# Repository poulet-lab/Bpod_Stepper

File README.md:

# Bpod Stepper Module

The *Bpod Stepper Module* enables virtually noiseless operation of a stepper motor by combining smooth acceleration profiles with a *SilentStepStick* driver. You can use it either as a module for *Bpod state machine r2* or as a stand-alone USB device.

## Wiki

Please refer to [**the wiki**](../../wiki) for documentation.

## Credits ##

* Concept & firmware by Florian Rau and Josh Sanders
* PCB layout by Christopher Schultz, Josh Sanders and Florian Rau
* PCB layout partially based on:
  * [Bpod Teensy Shield](https://github.com/sanworks/Bpod-CAD/tree/master/PCB/Modules/Gen2/Bpod%20Teensy%20Shield) by Sanworks ([GPL v3](https://www.gnu.org/licenses/gpl-3.0.en.html))
  * [SilentStepStick Protector](https://github.com/watterott/SilentStepStick) by Watterott ([CC BY-SA 4.0](https://creativecommons.org/licenses/by-sa/4.0/))
* Library dependencies:
  * [ArCOM](https://github.com/bimac/ArCOM) by Sanworks ([GPL v3](https://www.gnu.org/licenses/gpl-3.0.en.html))
  * [TeensyStep](https://github.com/luni64/TeensyStep) by luni64 ([MIT](https://opensource.org/licenses/MIT))
  * [TMCStepper](https://github.com/teemuatlut/TMCStepper) by teemuatlut ([MIT](https://opensource.org/licenses/MIT))
  * [Teensy3x_QuadDecode](https://github.com/bimac/Teensy3x_QuadDecode.git) by TLB ([MIT](https://opensource.org/licenses/MIT))

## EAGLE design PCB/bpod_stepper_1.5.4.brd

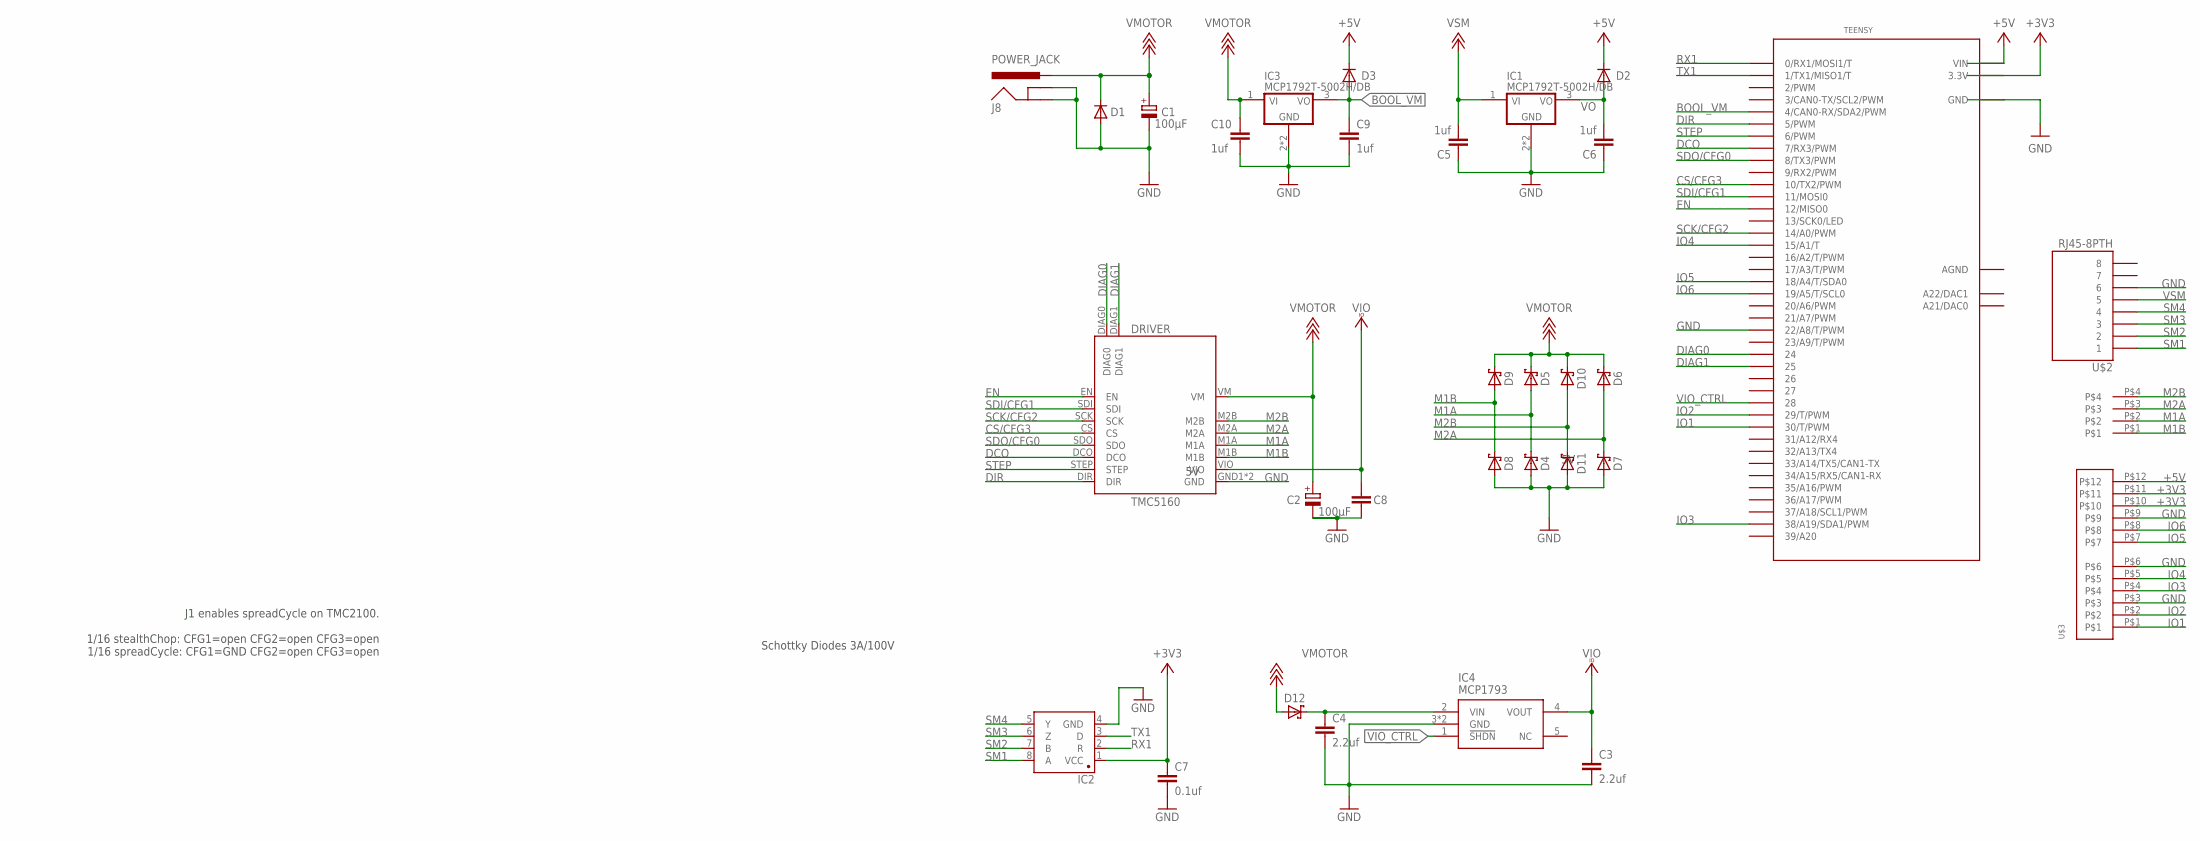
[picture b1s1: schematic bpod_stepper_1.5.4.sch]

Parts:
C1, C2: 100µF; PANASONIC_G
C3, C4: 2.2uf; 1206@1
C5, C6, C9, C10: 1uf; 1206@1
C7: 0.1uf; 1206@1
C8: 100nf; 1206@1
D1: DIODE-DO214AA; DO214AA
D2, D3: MBR0520LT; SOD123
D4, D5, D6, D7, D8, D9, D10, D11, D12: S310FA; SOD123
DRIVER: TMC5160
IC1, IC3: MCP1792T-5002H/DB; SOT223
IC2: SN65HVD31DR; SO08
IC4: MCP1793; SOT223-5
J8: POWER_JACK; POWER_JACK_PTH
TEENSY: TEENSY_3.6_DIL
U$2: RJ45-8PTH; RJ45-8
U$3: 12POS_MOLEX_SOCKET
U$4: MOLEX395221004

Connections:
+3V3: C7.1, IC2.1 (VCC), TEENSY.3.3V, TEENSY.3.3V3 (3.3V), U$3.P$10, U$3.P$11
+5V: D2.C, D3.C, TEENSY.VIN, U$3.P$12
AGND: TEENSY.AGND
BOOL_VM: C9.1, D3.A, IC3.3 (VO), TEENSY.4 (4/CAN0-RX/SDA2/PWM)
CS/CFG3: DRIVER.CS, TEENSY.10 (10/TX2/PWM)
DCO: DRIVER.DCO, TEENSY.7 (7/RX3/PWM)
DIAG0: DRIVER.DIAG0, TEENSY.24
DIAG1: DRIVER.DIAG1, TEENSY.25
DIR: DRIVER.DIR, TEENSY.5 (5/PWM)
EN: DRIVER.EN, TEENSY.12 (12/MISO0)
GND: C1.-, C2.-, C3.2, C4.2, C5.1, C6.1, C7.2, C8.2, C9.2, C10.2, D1.A, D4.A, D7.A, D8.A, D11.A, DRIVER.GND1 (GND), DRIVER.GND2 (GND), IC1.2 (GND), IC1.4 (GND), IC2.4 (GND), IC3.2 (GND), IC3.4 (GND), IC4.3 (GND), IC4.6 (GND), J8.GND, J8.GNDBREAK, TEENSY.22/A8 (22/A8/T/PWM), TEENSY.GND, TEENSY.GND1 (GND), U$2.6, U$3.P$3, U$3.P$6, U$3.P$9
IO1: TEENSY.30 (30/T/PWM), U$3.P$1
IO2: TEENSY.29 (29/T/PWM), U$3.P$2
IO3: TEENSY.38/A19 (38/A19/SDA1/PWM), U$3.P$4
IO4: TEENSY.15/A1 (15/A1/T), U$3.P$5
IO5: TEENSY.18/A4 (18/A4/T/SDA0), U$3.P$7
IO6: TEENSY.19/A5 (19/A5/T/SCL0), U$3.P$8
M1A: D4.C, D5.A, DRIVER.M1A, U$4.P$2
M1B: D8.C, D9.A, DRIVER.M1B, U$4.P$1
M2A: D6.A, D7.C, DRIVER.M2A, U$4.P$3
M2B: D10.A, D11.C, DRIVER.M2B, U$4.P$4
unnamed: C4.1, D12.C, IC4.2 (VIN)
RX1: IC2.2 (R), TEENSY.0 (0/RX1/MOSI1/T)
SCK/CFG2: DRIVER.SCK, TEENSY.14/A0 (14/A0/PWM)
SDI/CFG1: DRIVER.SDI, TEENSY.11 (11/MOSI0)
SDO/CFG0: DRIVER.SDO, TEENSY.8 (8/TX3/PWM)
SM1: IC2.8 (A), U$2.1
SM2: IC2.7 (B), U$2.2
SM3: IC2.6 (Z), U$2.3
SM4: IC2.5 (Y), U$2.4
STEP: DRIVER.STEP, TEENSY.6 (6/PWM)
TX1: IC2.3 (D), TEENSY.1 (1/TX1/MISO1/T)
VIO: C3.1, C8.1, DRIVER.VIO, IC4.4 (VOUT)
VIO_CTRL: IC4.1 (!SHDN), TEENSY.28
VMOTOR: C1.+, C2.+, C10.1, D1.C, D5.C, D6.C, D9.C, D10.C, D12.A, DRIVER.VM, IC3.1 (VI), J8.PWR
VO: C6.2, D2.A, IC1.3 (VO)
VSM: C5.2, IC1.1 (VI), U$2.5

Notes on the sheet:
Schottky Diodes 3A/100V
J1 enables spreadCycle on TMC2100. 1/16 stealthChop: CFG1=open CFG2=open CFG3=open 1/16 spreadCycle: CFG1=GND CFG2=open CFG3=open

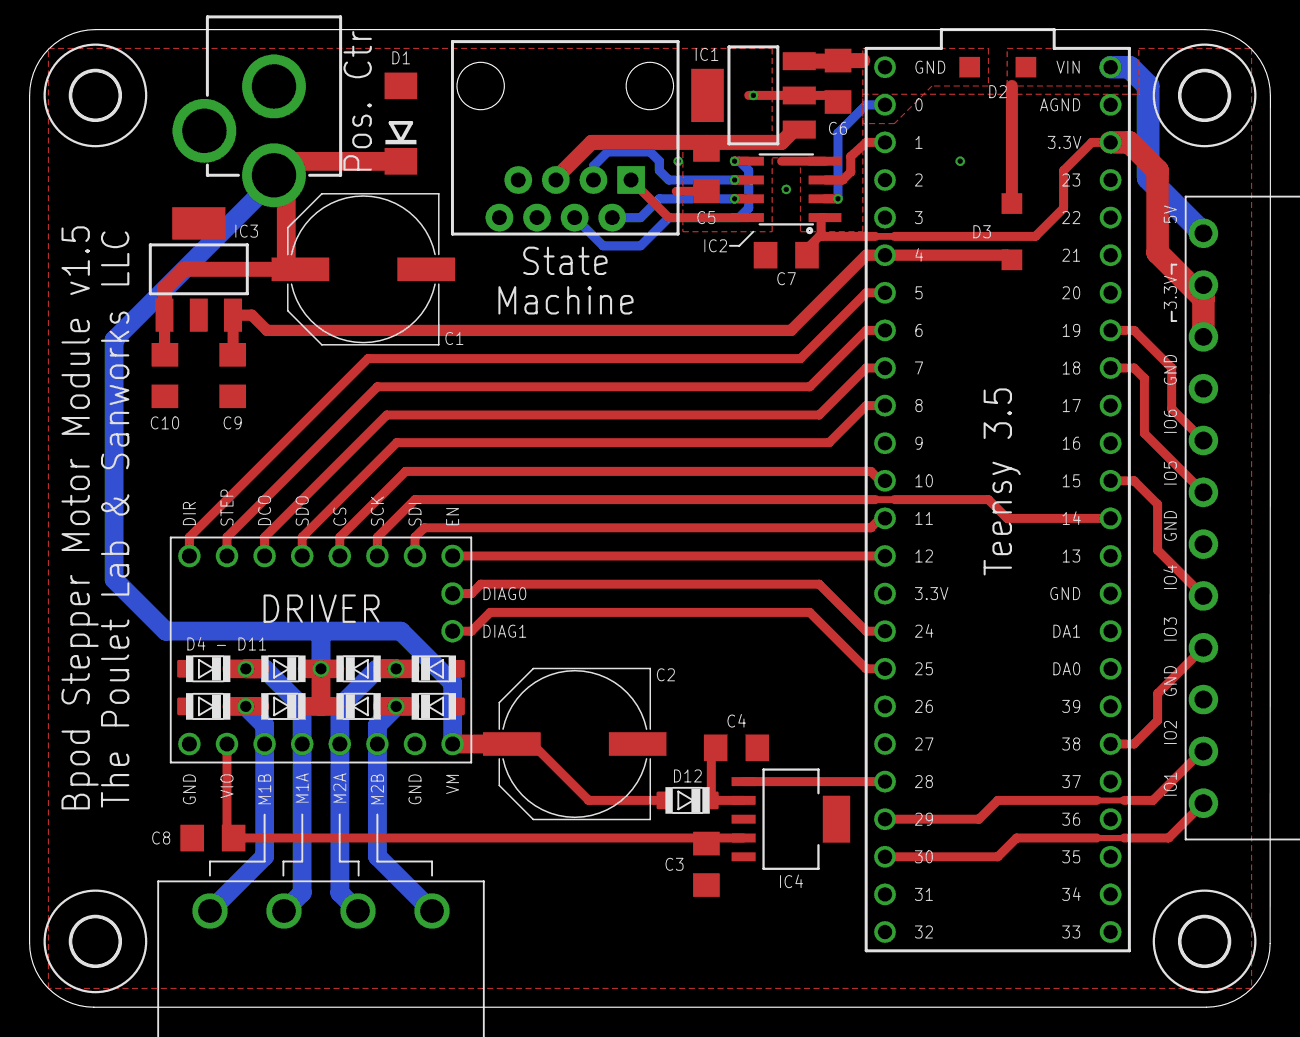
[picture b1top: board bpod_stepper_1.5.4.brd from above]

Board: 2 copper layers, 83.8 x 66.0 mm, 36 parts (0 on the bottom side), 36 nets.

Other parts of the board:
U$7, U$8, U$9, U$10: 3,2

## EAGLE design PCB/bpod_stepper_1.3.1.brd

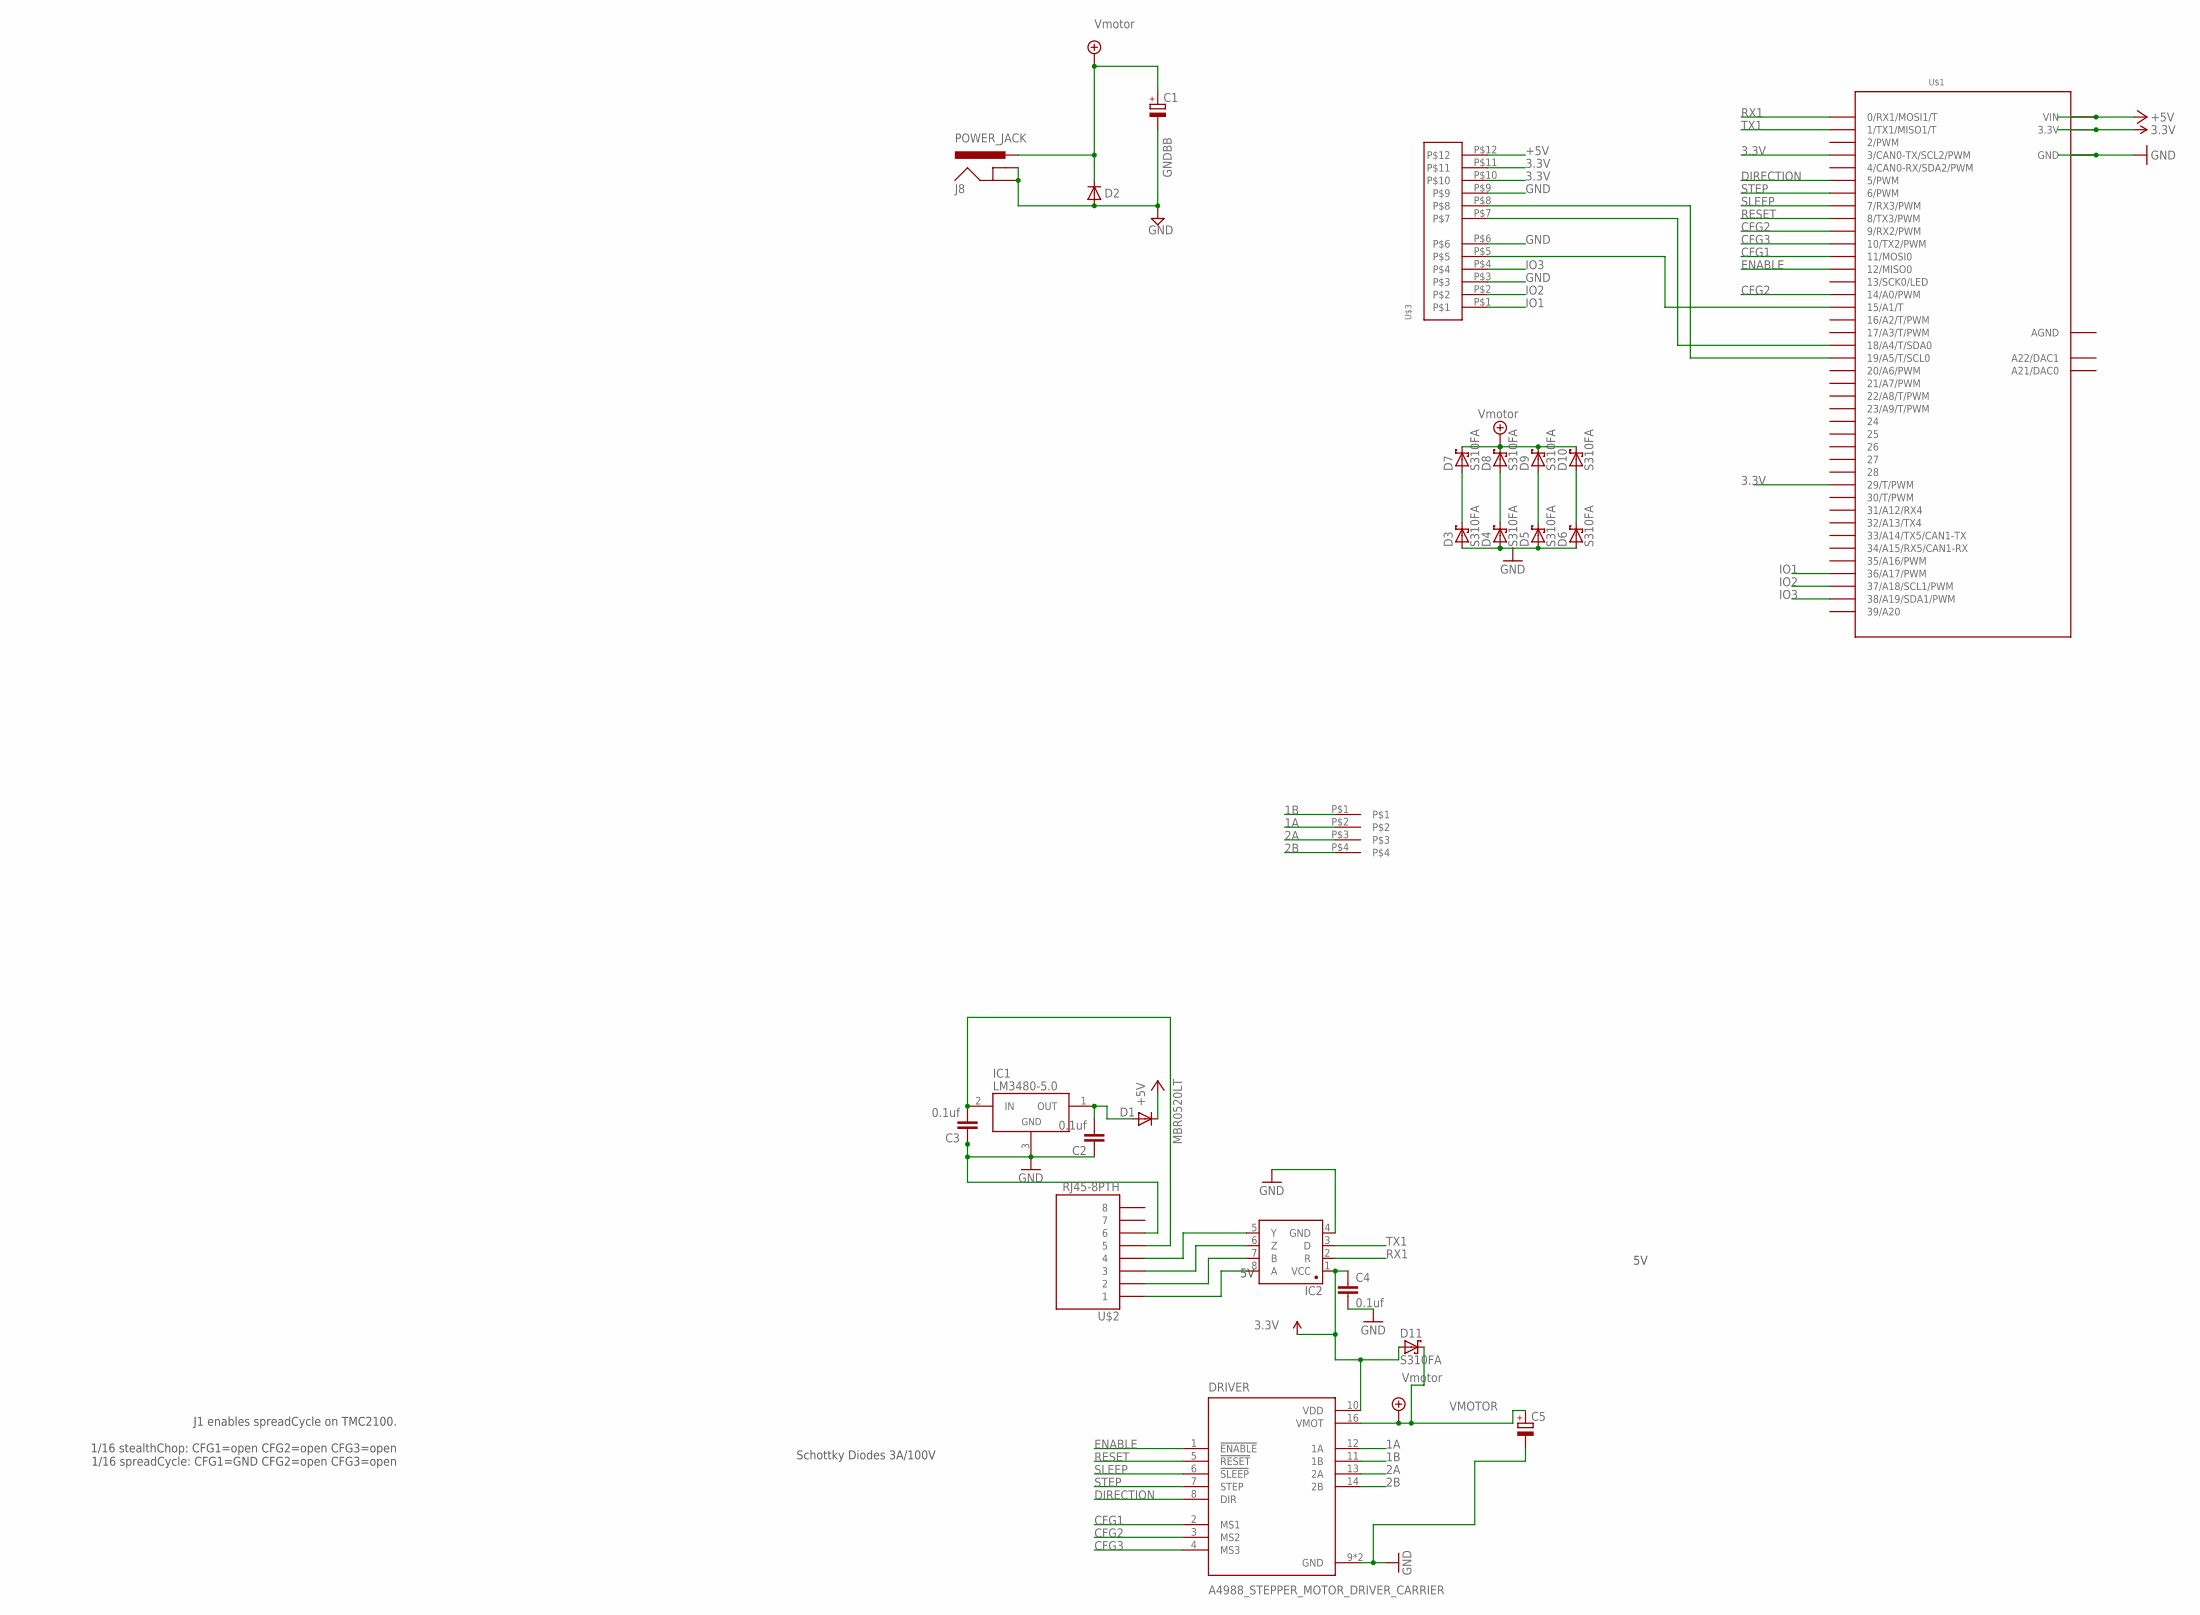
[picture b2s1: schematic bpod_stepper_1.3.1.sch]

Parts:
C1, C5: CPOL-EUG; PANASONIC_G
C2, C3, C4: 0.1uf; 1206@1
D1: MBR0520LT; SOD123
D2: DIODE-DO214AA; DO214AA
D3, D4, D5, D6, D7, D8, D9, D10, D11: S310FA; SOD123
DRIVER: A4988_STEPPER_MOTOR_DRIVER_CARRIER; MODULE_A4988_STEPPER_MOTOR_DRIVER_CARRIER
IC1: LM3480-5.0; SOT-23-3
IC2: SN65HVD31DR; SO08
J8: POWER_JACK; POWER_JACK_PTH
U$1: TEENSY_3.6_DIL
U$2: RJ45-8PTH; RJ45-8
U$3: 12POS_MOLEX_SOCKET
U$4: MOLEX395221004

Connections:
1A: D4.C, D8.A, DRIVER.12 (1A), U$4.P$2
1B: D3.C, D7.A, DRIVER.11 (1B), U$4.P$1
2A: D6.C, D10.A, DRIVER.13 (2A), U$4.P$3
2B: D5.C, D9.A, DRIVER.14 (2B), U$4.P$4
3.3V: C4.1, D11.A, DRIVER.10 (VDD), IC2.1 (VCC), U$1.3 (3/CAN0-TX/SCL2/PWM), U$1.3.3V, U$1.3.3V3 (3.3V), U$1.29 (29/T/PWM), U$3.P$10, U$3.P$11
+5V: D1.C, U$1.VIN, U$3.P$12
AGND: U$1.AGND
CFG1: DRIVER.2 (MS1), U$1.11 (11/MOSI0)
CFG2: DRIVER.3 (MS2), U$1.9 (9/RX2/PWM), U$1.14/A0 (14/A0/PWM)
CFG3: DRIVER.4 (MS3), U$1.10 (10/TX2/PWM)
DIRECTION: DRIVER.8 (DIR), U$1.5 (5/PWM)
ENABLE: DRIVER.1 (!ENABLE), U$1.12 (12/MISO0)
GND: C1.-, C2.1, C3.1, C4.2, C5.-, D2.A, D3.A, D4.A, D5.A, D6.A, DRIVER.9 (GND), DRIVER.15 (GND), IC1.3 (GND), IC2.4 (GND), J8.GND, J8.GNDBREAK, U$1.GND, U$1.GND1 (GND), U$2.6, U$3.P$3, U$3.P$6, U$3.P$9
IO1: U$1.36/A17 (36/A17/PWM), U$3.P$1
IO2: U$1.37/A18 (37/A18/SCL1/PWM), U$3.P$2
IO3: U$1.38/A19 (38/A19/SDA1/PWM), U$3.P$4
unnamed: U$1.19/A5 (19/A5/T/SCL0), U$3.P$8
unnamed: U$1.18/A4 (18/A4/T/SDA0), U$3.P$7
unnamed: U$1.15/A1 (15/A1/T), U$3.P$5
unnamed: IC2.8 (A), U$2.1
unnamed: IC2.7 (B), U$2.2
unnamed: IC2.6 (Z), U$2.3
unnamed: IC2.5 (Y), U$2.4
unnamed: C2.2, D1.A, IC1.1 (OUT)
unnamed: C3.2, IC1.2 (IN), U$2.5
RESET: DRIVER.5 (!RESET), U$1.8 (8/TX3/PWM)
RX1: IC2.2 (R), U$1.0 (0/RX1/MOSI1/T)
SLEEP: DRIVER.6 (!SLEEP), U$1.7 (7/RX3/PWM)
STEP: DRIVER.7 (STEP), U$1.6 (6/PWM)
TX1: IC2.3 (D), U$1.1 (1/TX1/MISO1/T)
VMOTOR: C1.+, C5.+, D2.C, D7.C, D8.C, D9.C, D10.C, D11.C, DRIVER.16 (VMOT), J8.PWR

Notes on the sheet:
GNDBB
Schottky Diodes 3A/100V
J1 enables spreadCycle on TMC2100. 1/16 stealthChop: CFG1=open CFG2=open CFG3=open 1/16 spreadCycle: CFG1=GND CFG2=open CFG3=open

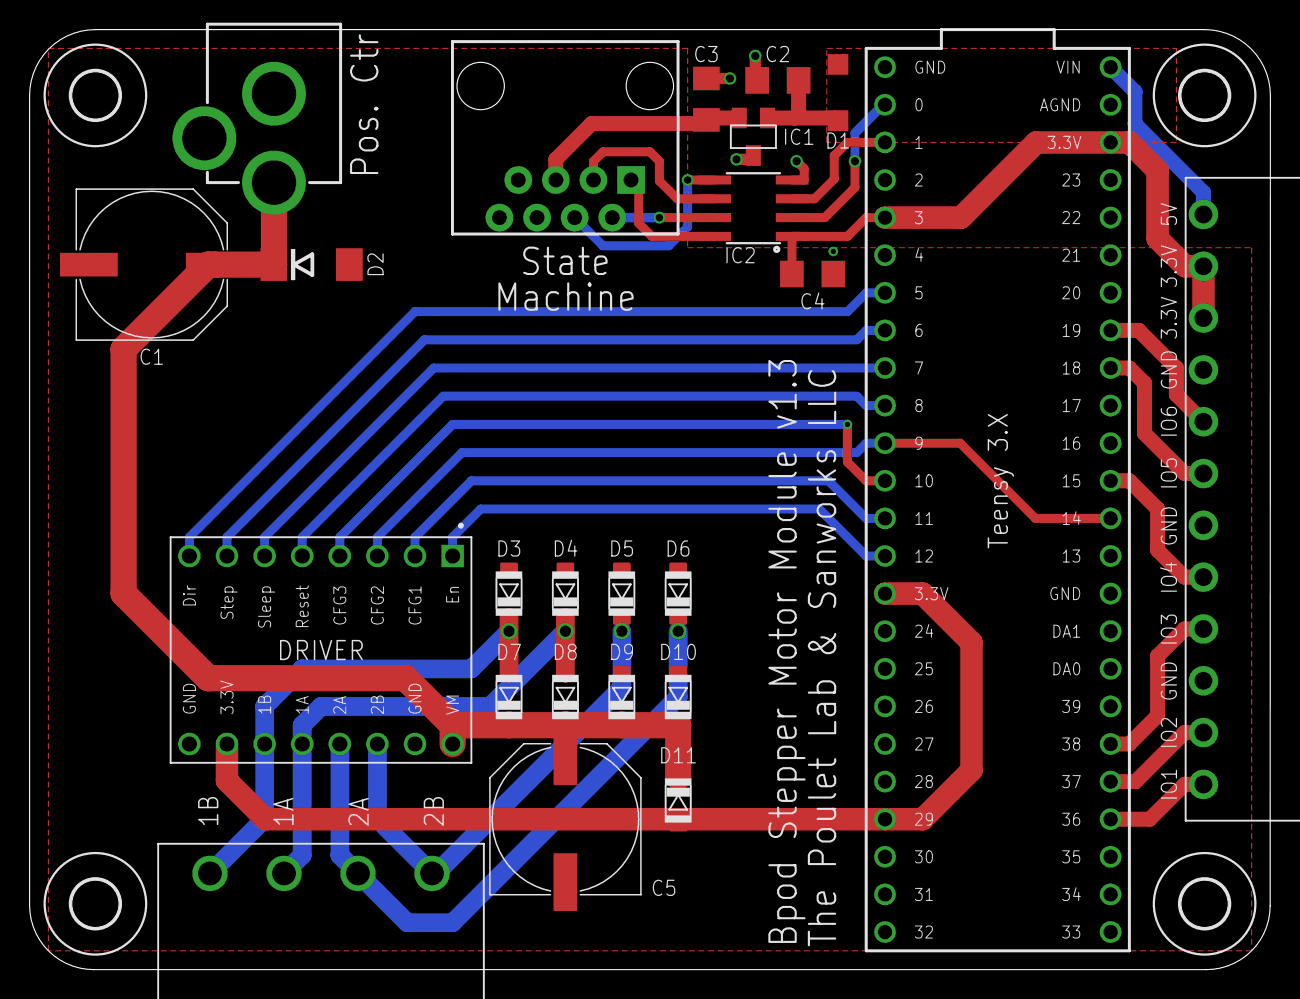
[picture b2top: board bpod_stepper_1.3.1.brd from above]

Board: 2 copper layers, 83.8 x 63.5 mm, 28 parts (0 on the bottom side), 30 nets.

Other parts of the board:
U$7, U$8, U$9, U$10: 3,2

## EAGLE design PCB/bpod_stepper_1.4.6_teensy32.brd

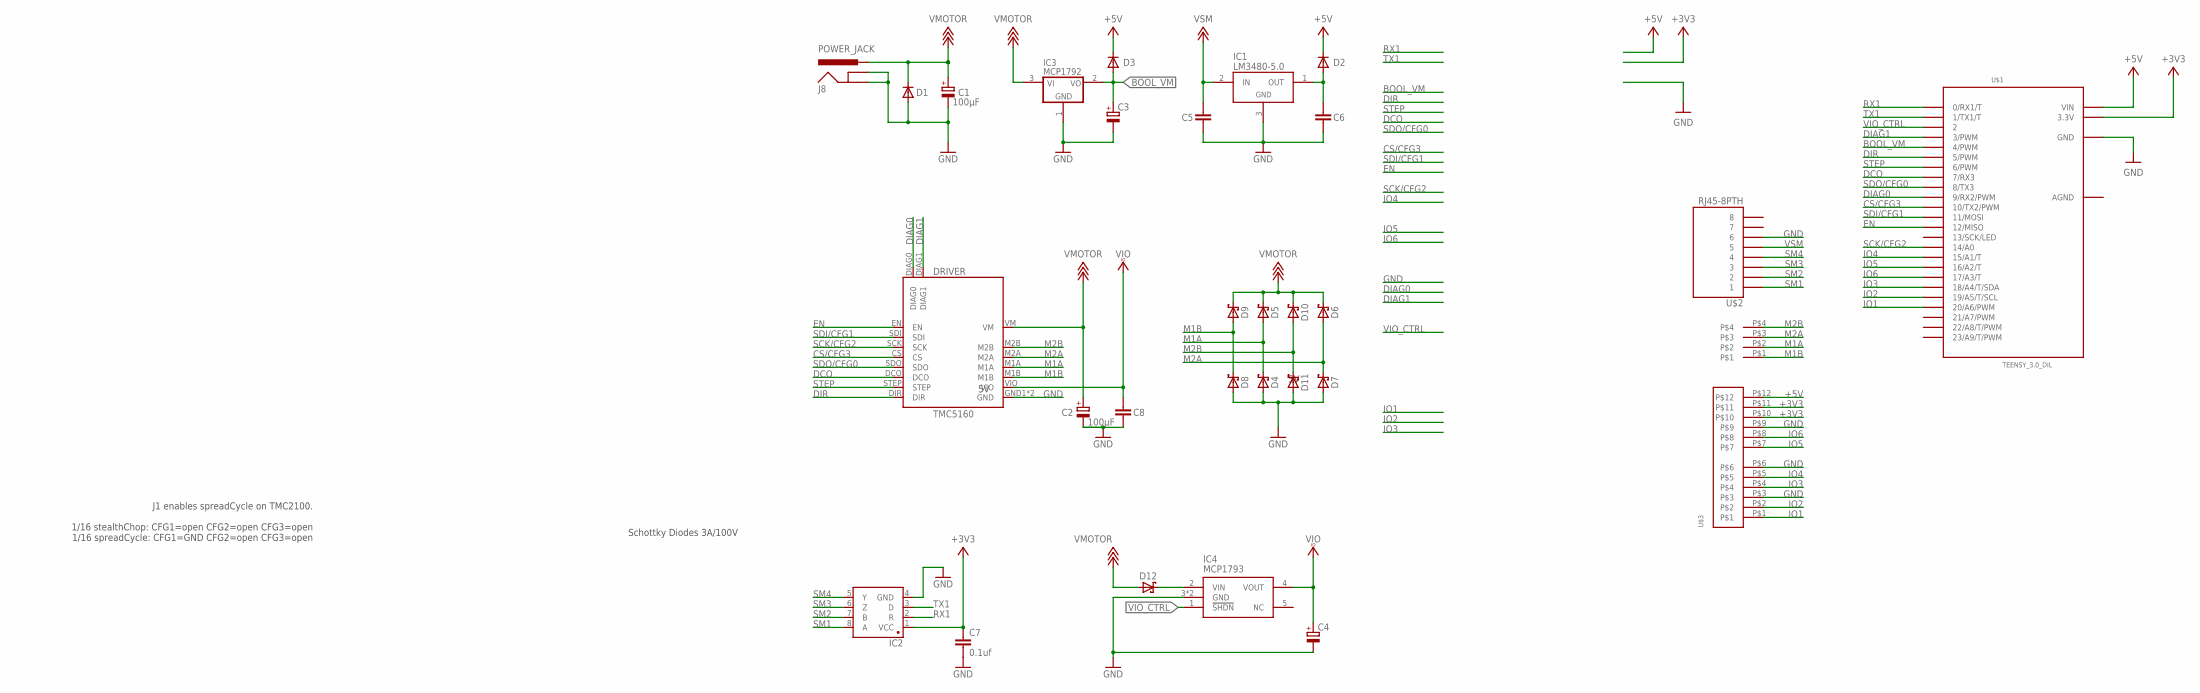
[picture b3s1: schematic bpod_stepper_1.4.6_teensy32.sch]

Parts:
C1, C2: 100µF; PANASONIC_G
C3, C4: CPOL-EUB; PANASONIC_B
C5, C6, C7: 0.1uf; 1206@1
C8: 100nf; 1206@1
D1: DIODE-DO214AA; DO214AA
D2, D3: MBR0520LT; SOD123
D4, D5, D6, D7, D8, D9, D10, D11, D12: S310FA; SOD123
DRIVER: TMC5160
IC1: LM3480-5.0; SOT-23-3
IC2: SN65HVD31DR; SO08
IC3: MCP1792; SOT23A_MICROCHIP_CB
IC4: MCP1793; SOT223-5
J8: POWER_JACK; POWER_JACK_PTH
U$1: TEENSY_3.0_DIL; TEENSY_3.0-3.2&LC_DIL
U$2: RJ45-8PTH; RJ45-8
U$3: 12POS_MOLEX_SOCKET
U$4: MOLEX395221004

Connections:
+3V3: C7.1, IC2.1 (VCC), U$1.3.3V, U$3.P$10, U$3.P$11
+5V: D2.C, D3.C, U$1.VIN, U$3.P$12
AGND: U$1.AGND
BOOL_VM: C3.+, D3.A, IC3.2 (VO), U$1.4 (4/PWM)
CS/CFG3: DRIVER.CS, U$1.10 (10/TX2/PWM)
DCO: DRIVER.DCO, U$1.7 (7/RX3)
DIAG0: DRIVER.DIAG0, U$1.9 (9/RX2/PWM)
DIAG1: DRIVER.DIAG1, U$1.3 (3/PWM)
DIR: DRIVER.DIR, U$1.5 (5/PWM)
EN: DRIVER.EN, U$1.12 (12/MISO)
GND: C1.-, C2.-, C3.-, C4.-, C5.1, C6.1, C7.2, C8.2, D1.A, D4.A, D7.A, D8.A, D11.A, DRIVER.GND1 (GND), DRIVER.GND2 (GND), IC1.3 (GND), IC2.4 (GND), IC3.1 (GND), IC4.3 (GND), IC4.6 (GND), J8.GND, J8.GNDBREAK, U$1.GND, U$2.6, U$3.P$3, U$3.P$6, U$3.P$9
IO1: U$1.20/A6 (20/A6/PWM), U$3.P$1
IO2: U$1.19/A5 (19/A5/T/SCL), U$3.P$2
IO3: U$1.18/A4 (18/A4/T/SDA), U$3.P$4
IO4: U$1.15/A1 (15/A1/T), U$3.P$5
IO5: U$1.16/A2 (16/A2/T), U$3.P$7
IO6: U$1.17/A3 (17/A3/T), U$3.P$8
M1A: D4.C, D5.A, DRIVER.M1A, U$4.P$2
M1B: D8.C, D9.A, DRIVER.M1B, U$4.P$1
M2A: D6.A, D7.C, DRIVER.M2A, U$4.P$3
M2B: D10.A, D11.C, DRIVER.M2B, U$4.P$4
unnamed: D12.C, IC4.2 (VIN)
unnamed: C6.2, D2.A, IC1.1 (OUT)
RX1: IC2.2 (R), U$1.0 (0/RX1/T)
SCK/CFG2: DRIVER.SCK, U$1.14/A0
SDI/CFG1: DRIVER.SDI, U$1.11 (11/MOSI)
SDO/CFG0: DRIVER.SDO, U$1.8 (8/TX3)
SM1: IC2.8 (A), U$2.1
SM2: IC2.7 (B), U$2.2
SM3: IC2.6 (Z), U$2.3
SM4: IC2.5 (Y), U$2.4
STEP: DRIVER.STEP, U$1.6 (6/PWM)
TX1: IC2.3 (D), U$1.1 (1/TX1/T)
VIO: C4.+, C8.1, DRIVER.VIO, IC4.4 (VOUT)
VIO_CTRL: IC4.1 (!SHDN), U$1.2
VMOTOR: C1.+, C2.+, D1.C, D5.C, D6.C, D9.C, D10.C, D12.A, DRIVER.VM, IC3.3 (VI), J8.PWR
VSM: C5.2, IC1.2 (IN), U$2.5

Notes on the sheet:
Schottky Diodes 3A/100V
J1 enables spreadCycle on TMC2100. 1/16 stealthChop: CFG1=open CFG2=open CFG3=open 1/16 spreadCycle: CFG1=GND CFG2=open CFG3=open

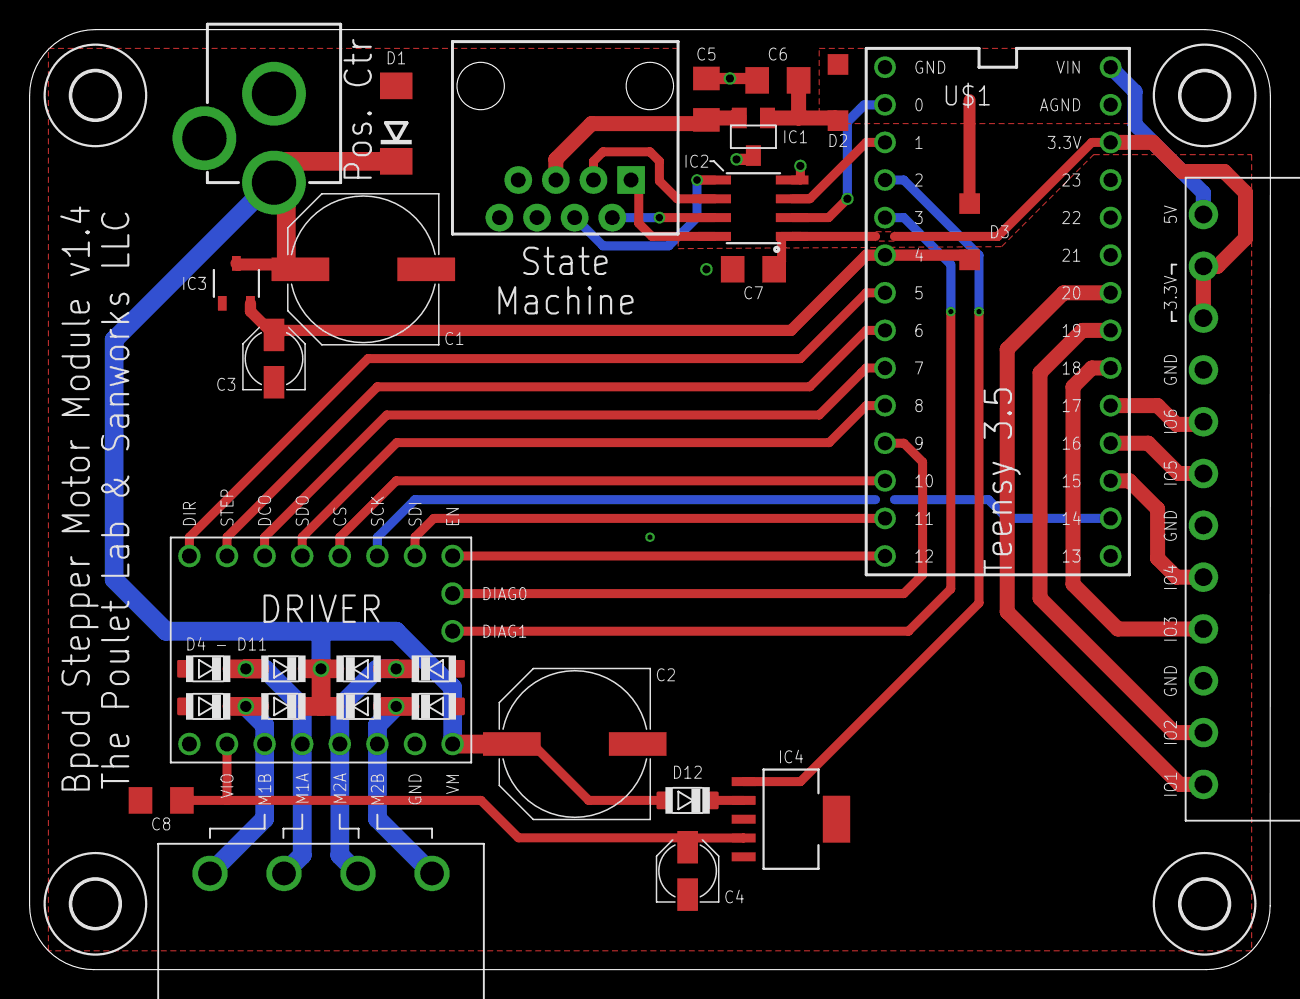
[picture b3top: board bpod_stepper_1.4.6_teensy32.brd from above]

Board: 2 copper layers, 83.8 x 63.5 mm, 34 parts (0 on the bottom side), 36 nets.

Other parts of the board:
U$7, U$8, U$9, U$10: 3,2

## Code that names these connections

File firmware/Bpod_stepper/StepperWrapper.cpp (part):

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  pinMode(pin.En, OUTPUT);
  pinMode(LED_BUILTIN, OUTPUT);
  if (PCBrev>=1.4) {
    pinMode(pin.VIO, OUTPUT);

    pinMode(pin.Diag0, INPUT_PULLUP);
    pinMode(pin.Diag1, INPUT_PULLUP);
    //attachInterrupt(digitalPinToInterrupt(pin.Diag0), ISRdiag0, RISING);
    //attachInterrupt(digitalPinToInterrupt(pin.Diag1), ISRdiag1, RISING);

    pinMode(pin.VM, INPUT);
    attachInterrupt(digitalPinToInterrupt(pin.VM), ISRchangeVM, CHANGE);
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  driver->diag1_stall(true);
  driver->diag0_int_pushpull(false);
  driver->diag1_pushpull(false);
  attachInterrupt(digitalPinToInterrupt(pin.Diag0), ISRdiag0, FALLING);
  attachInterrupt(digitalPinToInterrupt(pin.Diag1), ISRdiag1, FALLING);

  // RMS current
  driver->rms_current(rms_current,1);       // set motor current, standstill reduction disabled
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
void StepperWrapper::powerDriver(bool power) {
  DEBUG_PRINTF("Powering %s driver.\n",(power) ? "up" : "down");
  pinMode(pin.VIO, OUTPUT);
  if (PCBrev>=1.4) {
    digitalWrite(pin.VIO, power);
    delay(200);
  }
}
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    pin.Step  =  3;
    pin.Sleep =  4;
    pin.Reset =  5;
    pin.CFG3  =  6;
    pin.CFG2  =  7;
    pin.CFG1  =  8;
    pin.En    =  9;
    pin.IO[0] = 10;     // IO1 - watch out, zero indexing!
    pin.IO[1] = 11;     // IO2
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    pin.Step  =  5;
    pin.Sleep =  6;
    pin.Reset = 12;
    pin.CFG3  =  8;
    pin.CFG2  = 27;
    pin.CFG1  = 11;
    pin.En    = 24;
    pin.IO[0] = 36;     // IO1 - watch out, zero indexing!
    pin.IO[1] = 37;     // IO2
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    pin.Step  =  6;
    pin.Sleep =  7;
    pin.Reset =  8;
    pin.CFG3  = 10;
    pin.CFG2  = 14;
    pin.En    = 12;
    pin.IO[3] = 15;     // IO4
  }
  if (PCBrev >= 1.4) {  // r1.4: support for DIAG pins, VIO control and VM monitoring
    pin.Diag0 = 24;
    pin.Diag1 = 25;
    pin.VIO   = 28;
    pin.VM    = 4 ;
  }
  return pin;
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  if (!initialized) {
    powerDriver(true);
    if (PCBrev<1.3)
      driver = new TMC2130Stepper(pin.CFG3, 0.110, pin.CFG1, pin.Reset, pin.CFG2);
    else {
      driver = new TMC2130Stepper(pin.CFG3, 0.110);
      SPI.setMISO(pin.Reset);
      SPI.setMOSI(pin.CFG1);
      SPI.setSCK(pin.CFG2);
      SPI.begin();
    }
    delay(50);
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  if (!initialized) {
    powerDriver(true);
    if (PCBrev<1.3)
      driver = new TMC5160Stepper(pin.CFG3, 0.075, pin.CFG1, pin.Reset, pin.CFG2);
    else {
      driver = new TMC5160Stepper(pin.CFG3, 0.075);
      SPI.setMISO(pin.Reset);
      SPI.setMOSI(pin.CFG1);
      SPI.setSCK(pin.CFG2);
      SPI.begin();
    }
    delay(50);
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    return;
  enableDriver(false);
  errorID = ID;
  detachInterrupt(digitalPinToInterrupt(pin.Diag0));
  digitalWrite(pin.Error, HIGH);
  timerErrorBlink.begin(ISRblinkError, 250000);
}
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    default:    // TMC2100 (assumed)
      switch (ms) {
        case 16:
          pinMode(pin.CFG1, INPUT);
          pinMode(pin.CFG2, INPUT);
          break;
        case 4:
          pinMode(pin.CFG1, OUTPUT);
          digitalWrite(pin.CFG1, HIGH);
          pinMode(pin.CFG2, INPUT);
          break;
        case 2:
          pinMode(pin.CFG1, INPUT);
          pinMode(pin.CFG2, OUTPUT);
          digitalWrite(pin.CFG2, LOW);
          break;
        default:
          ms = 1;
          pinMode(pin.CFG1, OUTPUT);
          digitalWrite(pin.CFG1, LOW);
          pinMode(pin.CFG2, OUTPUT);
          digitalWrite(pin.CFG2, LOW);
      }
      _microsteps = ms;
  }
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void StepperWrapper::attachInput(uint8_t idx, void (*userFunc)(void)) {
  pinMode(pin.IO[idx], _ioResistor[idx]);
  uint8_t direction = (_ioResistor[idx]==INPUT_PULLUP) ? FALLING : RISING;
  attachInterrupt(digitalPinToInterrupt(pin.IO[idx]), userFunc, direction);
}

void StepperWrapper::toggleISRlimit(int8_t direction) {
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
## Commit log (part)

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2020-08-25 Add PCB designs
2020-08-26 Create LICENSE
2020-08-26 Rename bpod_stepper_v1_0.brd to PCB/bpod_stepper.brd
2020-08-26 Rename bpod_stepper_v1_0.sch to PCB/bpod_stepper.sch
2020-09-07 Update README.md
    Switched DC barrel jack for higher voltage rating
2020-09-28 add enclosure designs
2020-09-28 rename eagle files
2020-09-28 moved board.png
2020-09-28 update enclosure designs
2020-09-28 add initial version of firmware
2020-09-30 work on firmware ...
2020-09-30 modify copyright notice
2020-09-30 add inversion option for direction pin
2020-09-30 clean up
2020-10-01 remove RPM parts
2020-10-01 add routine for limit switches
2020-10-01 add option for inverted limit switches
2020-10-01 clean-up
2020-10-05 Update PCB & enclosure to v1.1
    - enlarged capacitors for Vmotor
    - removed 5V lines
2020-10-05 update enclosure design
2020-11-02 -Added MATLAB control class (untested) -Updated firmware to accept commands via USB (in addition to the state machine)
2020-11-04 -Fixed bug in BpodStepperModule limit switch function definition
2020-11-05 corrected wrong routing for RX & TX
2020-11-09 correct turnDegrees()
2020-11-09 attempt at removing some redundancies
2020-11-09 simplify loop()
2020-11-09 comments / clean-up
2020-11-10 corrected pointer comparisson
2020-11-10 consistently use ascii V for speed
2020-11-12 attach interrupt to limit switches
2020-11-12 Revert "attach interrupt to limit switches"
    This reverts commit 943bb127581417d88d153e89072d6d6259129414.
2020-11-12 Revert "update to SmoothStepper 1.0.2"
    This reverts commit 7e25a1b993fc331cb9cf911c8799bfeeead85d4e.
2020-11-12 update SmoothStepper
2020-11-12 switch to digitalWriteFast
2020-11-12 fire limit switch interrupt according to invertLimit
2020-11-12 move time critical commands to the front
2020-11-12 simplification
2020-11-12 use cstdint types
2020-11-12 keep track of last movement direction
2020-11-12 simplify findLimit()
2020-11-12 fix typo
2020-11-12 simplify things
2020-11-16 swapped in teensy 4.0
2020-11-16 format & documentation
2020-11-20 keep track of position
2020-11-21 add abbility to move to absolute positions
2020-12-31 initial EEPROM support
2020-12-31 drop uint32_t version
2021-01-03 move to EEstore class
2021-04-07 switch to teensystep
2021-04-17 -Added PCB design r1.2 that adds: 1. GPIO breakout to external screw terminal block, 2. Compatability with data features on TMC5160
2021-04-24 clean-up and minor adjustments
    - corrected board dimensions
    - clean-up
    - resized top ground-plane
    - updates to silkscreen
2021-04-26 -Updates to PCB design: Restricted ground plane from board edges, Restricted top ground plane from Bpod module interface circuitry and added vias to bottom plane, Rerouted UART traces to preserve bot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
2021-04-26 updated PCB
    - added molex connector (PN 0395221004)
    - further separation of motor and logic lines
2021-04-26 -Added minor revisions to 1.2.2 from PouletLab/Stepper restoring some features of 1.2.1
2021-08-18 Update Bpod_stepper.ino
    Update pin definitions for PCB 1.2.3
2021-08-19 PCB r1.3 with some reassigned pins
    - Dir: 5 (previously 4)
    - Step: 6 (previously 5)
    - Sleep: 7 (previously 6)
    - Reset/MISO: 8 (previously 12)
    - CFG3/CS: 10 (previously 8)
    - CFG2/SCK: 14 (via 9, previously 27)
2021-09-14 PCB revisions 1.3.1 and 1.4
2021-09-21 use 5V VIO for the stepper driver
2021-09-27 Create EEstore.h
    storing and receiving arbitrary data to EEPROM with CRC16
2021-09-27 slightly extended TMC5160Stepper class
    adds ability to write/clear RAMP_STAT
2021-09-27 First draft of StepperWrapper
2021-09-28 minor fix
2021-10-04 add get-methods for _a and _vMax
2021-10-04 various updates to the firmware
    - preliminary implementation of VM monitoring
    - return of serial communication
    - general clean-up & reorganization
2021-10-04 clean-up of MATLAB code
    - support for RMS current
    - reorganization of dependent properties
    - some documentation
2021-10-04 support for storing default configuration to EEPROM
2021-10-05 work on PCB
2021-10-07 vMax() and a() should return full-steps
2021-10-08 ignore temporary EAGLE files
2021-10-08 driver VIO from 3.3V regulator
2021-10-12 PCB 1.4.5 & updated BOM
2021-10-18 less convoluted mode of determining HW revision
2021-10-18 simplified layput of serial command interface
2021-10-18 seriall interface: presence of TMC5160
2021-10-25 predefined target positions
2021-10-25 target handling: optimize for short-circuit eval / use constrain() on user input
2021-10-25 minor clean-up
2021-10-25 reorganizing the code
2021-10-25 updated enclosure / fixed SVG size
2021-10-26 include sanworks logo
2021-10-26 correction for position of IO ports / use proper font
2021-10-26 reorganization of _PCBrev and _pin
2021-10-27 correct pin.VIO
2021-11-04 added D12 to prevent current flowing from pin 28 to pin 4
2021-11-08 support for TMC2130 / code-cleanup
2021-11-08 simplify handling of errorPin
2021-11-08 add D12 to BOM
2021-11-08 some work on error handling
2021-11-13 Updated BOM
2021-11-13 LED during movement
2021-11-13 events for start and stop of movement
2021-11-15 work on IO ports
2021-11-22 updated enclosure design
2021-11-23 minor updates to geometry / cut-outs
2021-11-29 implement support for TeensyStep library
2021-11-29 support for setting ChopperMode
2021-11-29 add softStop() and hardStop()
2021-12-01 added rotate() method
2021-12-01 rotate() - continued
2021-12-01 bind emergency stop to IO port
2021-12-01 more work on readme
2021-12-06 Bpod serial interface
2021-12-06 IO mode: rotate in direction
2021-12-06 IO mode: soft stop / simplification of interrupt logic
2021-12-13 improved logic for limit switches
    - dedicated interrupts for forward and backward movements
    - no start of movement when limit switch active
2022-01-07 wrong int type sent for ChopperMode
2022-01-07 Update BpodStepperModule.m
    correct implementation of rotate()
2022-01-07 correction for setting predefined target position
2022-01-10 forgot breaks in switch statement
2022-01-10 initial work on live streaming feature
2022-01-18 support array inputs for get/setMode and get/setResistor
2022-01-24 write position to SD
2022-01-24 bugfix for softStop()
2022-01-24 avoid superfluous writes to SD
2022-01-24 better readability for output of getTarget()
2022-01-25 output formatting / support for multiple targets for setTarget() & getTarget()
2022-01-27 reorganization of EEstore.h
2022-01-27 predefined targets now with individual vMax and acceleration
2022-01-27 minor simplifications
2022-01-28 speed optimizations
2022-02-16 Squashed commit of the following:
    commit bb7b450f647cebed25347bc011dd67f2798218c8
    Author: Florian Rau <bimac@users.noreply.github.com>
    Date: Thu Feb 17 00:27:25 2022 +0100
    Fixing massive headache with micro-positioning
    commit acb3d993700eefe6f983e04bd046d38e9035e620
    Author: Florian Rau <bimac@users.noreply.github.com>
2022-02-17 more clean-up
2022-02-17 keep a few extra samples to improve the scrolling effect
2022-02-23 Cleaning up
2022-03-02 add luni64's TeensyStep to credits
2022-03-09 remove unnecessary debug flags
2022-03-09 fix bug in positioning
2022-03-09 discontinuous line if samples were skipped
2022-03-09 support serial communication during streaming mode
2022-03-14 package firmware for platform.io
2022-03-15 converted INO to CPP
2022-03-15 handle DEBUG flag via project environment
2022-03-15 define ArCOM as external library
2022-03-16 add soft-stop callback for _rotateControl
2022-03-16 fix for tmc2100
2022-03-27 hexadecimal notation only supported from R2019b onwards
2022-03-27 allow for custom parent handles
2022-04-20 use ArCOM v2
2022-04-20 fixed DeleteFcn for live mode
2022-04-27 add environment for jlink probe
2022-04-27 correct missing initialization for _microsteps
2022-05-03 add support for quadrature encoder
2022-05-03 switch to QuadDecode library
2022-05-04 -Afternoon update
    Revised text
2022-05-04 Added error if multiple serial ports are available and one was not specified
    Added error if multiple serial ports are available and one was not specified
2022-05-04 only show EncoderPosition property when using an encoder
2022-05-04 some cleanup
2022-05-04 yet another correction for buggy (micro-)positioning
2022-05-11 PCB rev 1.5.0
    - Increased board dimensions
    - Swapped two 5V regulators to MCP1792T-5002H/DB
    - Rerouted IO1 and IO2 for compatibility with hardware quadrature encoder
    - Incremented version number
2022-05-12 PCB rev 1.5.1
    - routed IO1 and IO2 through pins
    - decreased width of board to its original value
2022-05-13 PCB rev 1.5.2
    - some corrections to silkscreen
    - alignment of barrel jack
2022-05-18 correction of property display
2022-05-18 correct pin definition for PCB rev 1.5
2022-05-18 enable micro-stepped positioning / reorganize & simplify code
2022-06-09 PCB r1.5.3
    corrected alignment of I/O ports
2022-06-09 enclosure for v1.5
2022-06-14 Update to TeensyStep enables debugging with -O0
2022-06-14 change PCBrev from float to uint_8t
2022-06-14 keep track of stepper and encoder resolutions
2022-06-14 Feat/encoder (#4)
    * add support for quadrature encoder
    * switch to QuadDecode library
    * only show EncoderPosition property when using an encoder
    * correction of property display
    * correct pin definition for PCB rev 1.5
    * correction of property display - again
2022-06-14 Revert "Merge branch 'master' into feat/encoder"
    This reverts commit 334a59fc887a118c55da8c2e2aefc17528980917, reversing
    changes made to 255d939cb33ea68fce392fd7602fa9700544200a.
2022-06-14 Revert "Feat/encoder (#4)"
    This reverts commit bba3a4f331cdfc3fe15fbe5685656ed6dab4b752.
2022-06-14 drop support for TMC2100
2022-06-14 Revert "Revert "Merge branch 'master' into feat/encoder""
    This reverts commit e8b787a4a0d770befef3abf9346529d7f2fad731.
2022-06-14 sorry for the mess ...
2022-06-16 correct size limitation for attributes of setTarget()
2022-06-20 Create workspace.code-workspace
2022-08-30 add DEBUG_WAIT
2022-09-29 returnModuleInfo() now supports HW info
2022-10-12 Update BOM
2022-10-17 Added PCB version 1.5.4 with the following changes: -Removed C3, C4 (electrolytic caps on outputs of IC3, IC4) -Added C3, C4 (ceramic 2.2uf caps on IC4 input and output) -Added C9, C10 (ceramic 1.1uf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
2022-10-18 some clean-up, undo version increment
2022-10-18 PCB revision 1.5.4 (#5)
    * Added PCB version 1.5.4 with the following changes:
    -Removed C3, C4 (electrolytic caps on outputs of IC3, IC4)
    -Added C3, C4 (ceramic 2.2uf caps on IC4 input and output)
    -Added C9, C10 (ceramic 1.1uf caps on IC3 input and output)
    -Updated values of C4, C5 from 0.1uf to 1.0uf for use with MCP1799T-5002H/DB
2022-11-09 add functionSignatures.json
2022-11-09 add lower limits for rms_current()
2022-11-09 default values for step() and microStep()
2022-11-16 control of hold current
2022-11-22 serial_debug builds with dual serial ports
2022-11-22 bug-fix: motor doesn't turn after start-up
2022-11-22 cleanup and readability
2023-02-13 major clean-up
2023-02-17 convert fonts to curves
2023-02-17 Revert "convert fonts to curves"
    This reverts commit b278654b51dc06c3065884658c2ef152c318bb5e.
2023-02-22 Revert "major clean-up"
    This reverts commit 2ff23546487e158650a096977fca89e92f48b85f.
2023-03-27 more cleaning
2023-04-11 Squashed commit of the following:
    commit 72e4d6ae8f8d41f057527c39be8038e63382b474
    Author: Florian Rau <bimac@users.noreply.github.com>
    Date: Tue Apr 11 23:45:01 2023 +0200
    almost!
    commit 262aee6bf922607248ab955985eb8a3e2609e70b
    Author: Florian Rau <bimac@users.noreply.github.com>
2023-04-12 automatic formatting
2023-04-12 Revert "Revert "major clean-up""
    This reverts commit fb0b465d4f71cd8352c45875c9491a14c25e1c2b.
2023-04-12 major clean-up (2nd attempt)
2023-05-23 Minor Fixes
    - remove SmoothStepper dependency
    - formatting & typos
    - issue with private copy of storageVars
2023-05-23 add support for *relative* predefined targets
2023-05-23 increase default PWM frequency
2023-05-23 update MATLAB class
    - improved legibility of object properties
    - switch to higher precision positioning
    - formatting

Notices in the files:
firmware/Bpod_stepper/StepperWrapper.cpp:
Copyright (C) 2021 Florian Rau
This program is free software: you can redistribute it and/or modify it under
the terms of the GNU General Public License as published by the Free Software
parts and their libraries:
SparkFun-Capacitors: Licensing: Creative Commons ShareAlike 4.0 International - https://creativecommons.org/licenses/by-sa/4.0
SparkFun: Licensing: CC v3.0 Share-Alike You are welcome to use this library for commercial purposes.
